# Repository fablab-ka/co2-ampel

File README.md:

# CO2-Ampel V2
![CO2-Ampel][co2ampel]

## Einleitung
Der CO2-Gehalt der Luft kann als Indikator benutzt werden, um das Raumklima zu überwachen und eine potentielle Virenlast in geschlossenen Räumen zu erkennen. In freier Natur und in frisch gelüfteten Räumen beträgt er ungefähr 400ppm (0,04%). In geschlossenen Räumen mit anwesenden Personen steigt er konstant an. Ab ca. 1500ppm wird das Raumklima schlecht, und es können Unbehaglichkeit, Müdigkeit und Konzentrationsschwächen auftreten. 

Da Viren, die als Aerosol übertragen werden, zusammen mit dem CO2 in den Raum gebracht werden, kann über den CO2-Gehalt der Raumluft als Indikator für das Ansteckungsrisiko dienen.

Mithilfe von CO2-Sensoren lässt sich der CO2-Gehalt der Raumluft überwachen. Viele vorhandenen Geräte erlauben zwar eine akkurate Messung, zeigen aber die Auswirkungen auf die Raumluft nur mit kleinen LED-Anzeigen oder überhaupt nicht an. Sie eignen sich daher nur bedingt für den Einsatz in Gruppenräumen.

## Zielsetzung
Die *CO2-Ampel V2* wurde speziell für Schulen und Kitas entwickelt. Sie zeigt das Raumklima spielerisch und gut sichtbar im Stil einer Verkehrsampel an. *Grün* bedeutet *alles in Ordnung*. Springt die Ampel auf *gelb*, wird es Zeit, die Fenster zu öffnen. Bei *rot* ist der Grenzwert überschritten. Ein akustisches Signal weist zusätzlich darauf hin, dass nunmehr umgehend gelüftet werden muss. Sobald der CO2-Gehalt sich normalisiert hat, springt die Ampel wieder auf *grün*. Ein lachender bzw. ein trauriger Smiley illustrieren das Messergebnis zusätzlich.

Das Gerät lässt sich leicht installieren und wird über ein gewöhnliches USB-Kabel mit Strom versorgt. Der eingebaute Sensor erlaubt präzise CO2-Messungen. Auf Wunsch lässt sich der Verlauf der Messwerte per WLAN in einem Web-Interface anzeigen und protokollieren.

Bei der CO2-Ampel V2 handelt es sich um ein gemeinsames Projekt des [FabLab Karlsruhe e.V.](https://fablab-karlsruhe.de) und des [FabLab Bruchsal e.V.](http://fablab-bruchsal.de) im Rahmen der Aktion [Corona-Hilfe Karlsruhe](https://coronahilfe-karlsruhe.de).

## Inbetriebnahme und Fehlerbehebung
Die [Bedienungsanleitung](Documentation/Deutsch/Bedienungsanleitung.md) der CO2-Ampel V2 erläutert alle erforderlichen Schritte zur Inbetriebnahme und zur Nutzung einer fertigen CO2-Ampel. Sie deckt die folgenden Aspekte ab:

* Installation und Stromversorgung
* Optische und akustische Signale
* Konfiguration der WLAN-Verbindung (optional)
* Zugriff auf die Messdaten und Protokolle (optional)
* Fehlerbehebung
* Technische Daten
* Entsorgung

## Aufbauanleitung (Bausatz)
Die bebilderte [Aufbauanleitung](Documentation/Deutsch/Aufbauanleitung.md) erklärt Schritt für Schritt, wie die CO2-Ampel aus den Einzelkomponenten zusammengesetzt wird. Dies umfasst die folgenden Schritte:

* Einstecken des Microcontrollers und des CO2-Sensors
* Einsetzen der Platine
* Zusammenstecken und Verschrauben des Geräts

## Beschaffung bzw. Herstellung der Komponenten
Die [Herstellungsanleitung](Documentation/Deutsch/Herstellungsanleitung.md) gibt einen Überblick, wie die Einzelkomponenten der CO2-Ampel basierend auf den Informationen in diesem GitHub-Repository hergestellt bzw. beschafft werden können. Die Anleitung umfasst die folgenden Abschnitte:

* Beschaffung der Bauteile
* Bestellung der Platine bei einem PCB-Haus
* Bestückung der Platine mit den SMD-Komponenten
* Einlöten der weiteren elektronischen Komponenten
* Kompilieren und Hochladen der Software
* Einrichtung des Webinterfaces für den Datenzugriff
* 3D-Druck des Gehäuses

In der bebilderten [Loetanleitung](Documentation/Deutsch/Loetanleitung) sind alle wichtigen Schritte zum Löten der Komponenten beschrieben. Wir haben uns hier auf das Einlöten der Through Hole Komponenten beschränkt.

## Weiterentwicklung des Projekts
Der gesamte Quellcode der CO2-Ampel V2 wurde in diesem  GitHub-Repository veröffentlicht. Er besteht aus den folgenden Komponenten:

* Platine ([Gerber](https://de.wikipedia.org/wiki/Gerber-Format))
* Software (c++)
* Gehäuse (Wahlweise [Autodesk Fusion 360](https://www.autodesk.de/products/fusion-360/overview) oder [OpenSCAD](https://www.openscad.org))

## Zusätzliche Ressourcen
  * https://wiki.fablab-karlsruhe.de/doku.php?id=projekte:2020:co2-ampel

[co2ampel]: images/co2ampel.jpg "CO2-Ampel"

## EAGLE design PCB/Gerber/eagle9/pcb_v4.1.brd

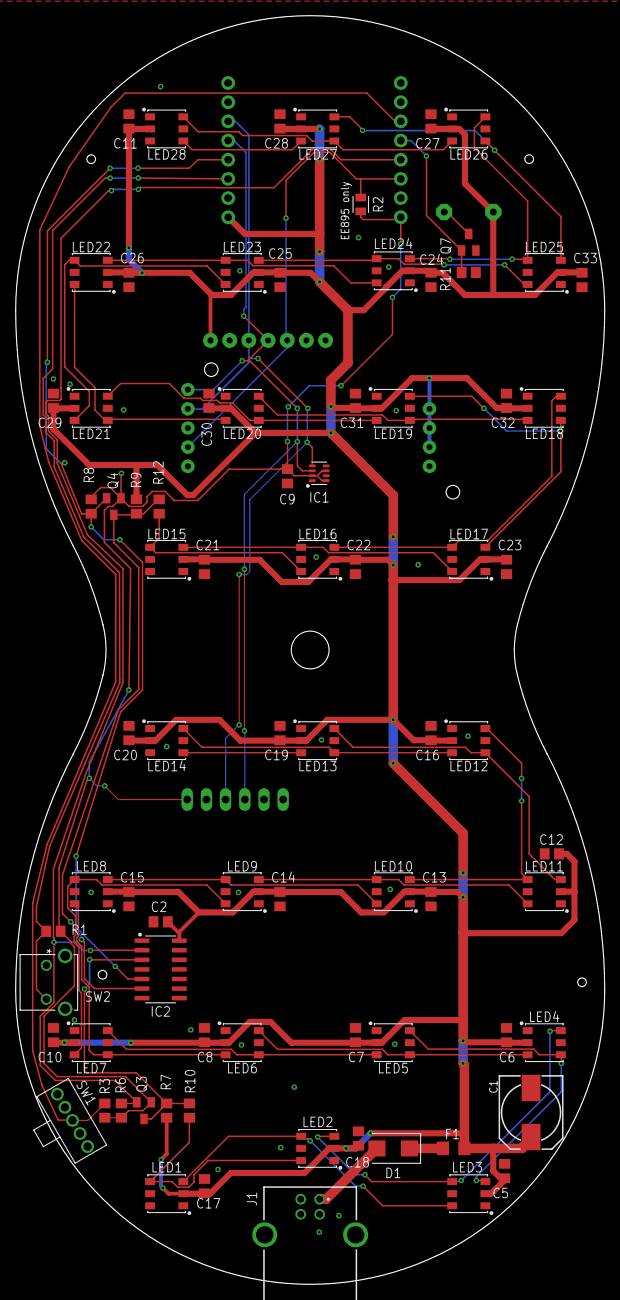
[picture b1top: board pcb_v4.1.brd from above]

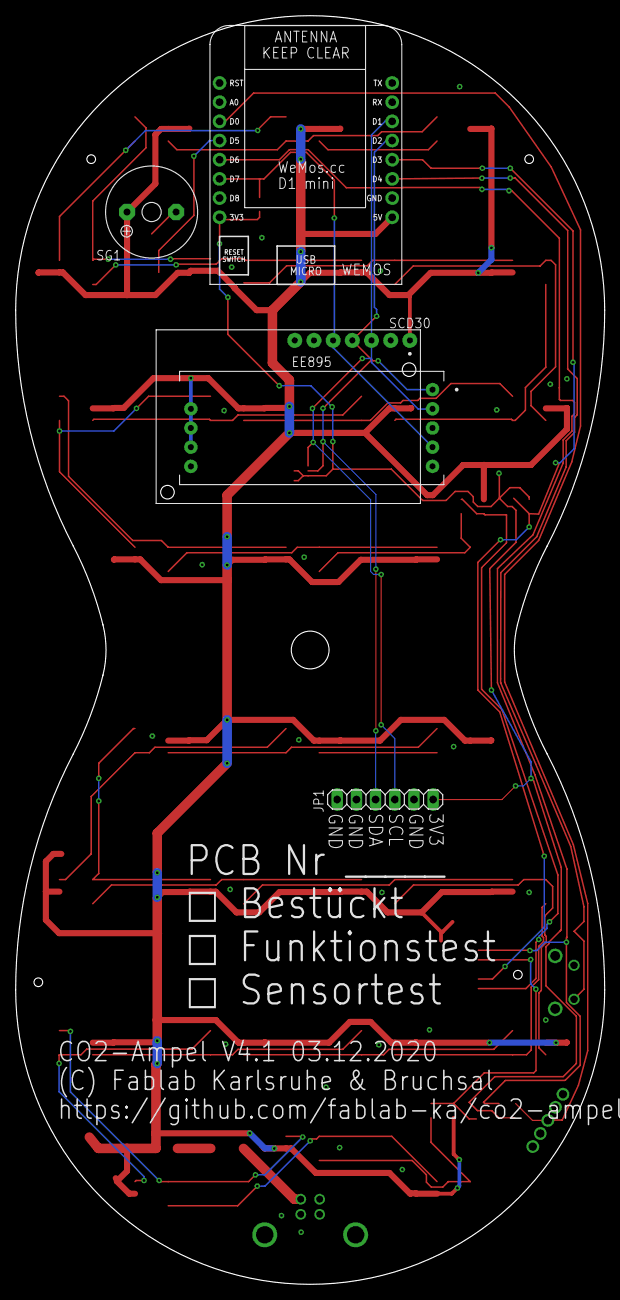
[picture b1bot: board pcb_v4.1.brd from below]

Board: 2 copper layers, 78.0 x 168.0 mm, 84 parts (5 on the bottom side), 44 nets.

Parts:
C1: 1m; 140CLH-0810
C2, C5, C6, C7, C8, C9, C10, C11, C12, C13, C14, C15, C16, C17, C18, C19, C20, C21, C22, C23, C24, C25, C26, C27, C28, C29, C30, C31, C32, C33: 100n; C0805
D1: SS24; DIOM5336X265N
EE895: EE895; DIP3200W60P254L1500H700Q10A
F1: 1206L110THYR; R1206
IC1: BMP280; SON65P200X250X95-8N
IC2: SN74AHCT125; SOIC127P600X175-14N
J1: C46392; 61400416121
JP1: PINHD-1X6; 1X06
LED1, LED2, LED3, LED4, LED5, LED6, LED7, LED8, LED9, LED10, LED11, LED12, LED13, LED14, LED15, LED16, LED17, LED18, LED19, LED20, LED21, LED22, LED23, LED24, LED25, LED26, LED27, LED28: WS2813; SON160P500X500X150-6N
Q3, Q4, Q7: DMG2302UK-7; SOT23
R1, R3, R6, R8, R11: 4.7k; R0805
R2: 4,7k; RESC2012X65
R7, R9: 1k; R0805
R10, R12: 470R; R0805
SCD30: SDC30; HDRV7W80P254_1X7_1778X254X838B
SG1: YS-MBZ12085C05R42; KSS1201
SW1: SWITCH_1X1; HDRRAR5W64P200_1X5_1016X736X556B
SW2: 1-1825027-4; SW2_1825027-E
WEMOS: WEMOS_D1_MINI; HDRVR8W64P254_1X8_2032X254X850B

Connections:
+3V3: C9.1, IC1.2, IC1.6, IC1.8, JP1.1, Q3.1, Q4.1, R1.2, R2.2, R3.2, R6.2, R8.2, WEMOS.3V3
+5V: C1.+, C2.1, C5.1, C6.1, C7.1, C8.1, C10.1, C11.1, C12.1, C13.1, C14.1, C15.1, C16.1, C17.1, C18.1, C19.1, C20.1, C21.1, C22.1, C23.1, C24.1, C25.1, C26.1, C27.1, C28.1, C29.1, C30.1, C31.1, C32.1, C33.1, EE895.7, EE895.8, EE895.9, F1.2, IC2.14, LED1.2, LED2.2, LED3.2, LED4.2, LED5.2, LED6.2, LED7.2, LED8.2, LED9.2, LED10.2, LED11.2, LED12.2, LED13.2, LED14.2, LED15.2, LED16.2, LED17.2, LED18.2, LED19.2, LED20.2, LED21.2, LED22.2, LED23.2, LED24.2, LED25.2, LED26.2, LED27.2, LED28.2, R7.2, R9.2, SCD30.1, SG1.+, WEMOS.5V
BUZZER: Q7.1, R11.2, WEMOS.D5
BUZZ_EN: R3.1, SW1.3, WEMOS.D0
GND: C1.-, C2.2, C5.2, C6.2, C7.2, C8.2, C9.2, C10.2, C11.2, C12.2, C13.2, C14.2, C15.2, C16.2, C17.2, C18.2, C19.2, C20.2, C21.2, C22.2, C23.2, C24.2, C25.2, C26.2, C27.2, C28.2, C29.2, C30.2, C31.2, C32.2, C33.2, EE895.3, EE895.5, EE895.6, IC1.1, IC1.5, IC1.7, IC2.1, IC2.4, IC2.7, IC2.10, IC2.13, J1.4, JP1.2, JP1.5, JP1.6, LED1.5, LED1.6, LED2.5, LED3.5, LED4.5, LED5.5, LED6.5, LED7.5, LED8.5, LED9.5, LED10.5, LED11.5, LED12.5, LED13.5, LED14.5, LED15.5, LED15.6, LED16.5, LED17.5, LED18.5, LED19.5, LED20.5, LED21.5, LED22.5, LED23.5, LED24.5, LED25.5, LED26.5, LED27.5, LED28.5, Q7.2, R11.1, SCD30.2, SW1.4, SW2.1, WEMOS.GND
LED_DATA_1: IC2.2, Q3.2, R6.1, WEMOS.D6
LED_DATA_2: IC2.5, Q4.2, R8.1, WEMOS.D3
unnamed: IC2.3, Q3.3, R7.1, R10.1
unnamed: LED2.3, LED3.4, LED4.6
unnamed: LED1.3, LED2.4, LED3.6
unnamed: LED4.3, LED5.4, LED6.6
unnamed: D1.1, F1.1
unnamed: LED3.3, LED4.4, LED5.6
unnamed: LED8.3, LED9.4, LED10.6
unnamed: LED5.3, LED6.4, LED7.6
unnamed: LED6.3, LED7.4, LED8.6
unnamed: LED7.3, LED8.4, LED9.6
unnamed: LED16.3, LED17.4, LED18.6
unnamed: LED9.3, LED10.4, LED11.6
unnamed: LED10.3, LED11.4, LED12.6
unnamed: LED11.3, LED12.4, LED13.6
unnamed: LED12.3, LED13.4, LED14.6
unnamed: LED13.3, LED14.4
unnamed: LED15.4, LED16.6, R12.2
unnamed: LED15.3, LED16.4, LED17.6
unnamed: LED24.3, LED25.4, LED26.6
unnamed: D1.2, J1.1
unnamed: LED17.3, LED18.4, LED19.6
unnamed: LED18.3, LED19.4, LED20.6
unnamed: LED19.3, LED20.4, LED21.6
unnamed: LED20.3, LED21.4, LED22.6
unnamed: LED21.3, LED22.4, LED23.6
unnamed: LED22.3, LED23.4, LED24.6
unnamed: LED23.3, LED24.4, LED25.6
unnamed: Q7.3, SG1.-
unnamed: LED25.3, LED26.4, LED27.6
unnamed: LED26.3, LED27.4, LED28.6
unnamed: LED27.3, LED28.4
RDY: EE895.4, R2.1, SCD30.5, WEMOS.D7
SCHALTER: R1.1, SW2.2, WEMOS.D4
SCL: EE895.2, IC1.4, JP1.3, SCD30.3, WEMOS.D1
SCL1: LED1.4, LED2.6, R10.2
SCL2: IC2.6, Q4.3, R9.1, R12.1
SDA: EE895.1, IC1.3, JP1.4, SCD30.4, WEMOS.D2

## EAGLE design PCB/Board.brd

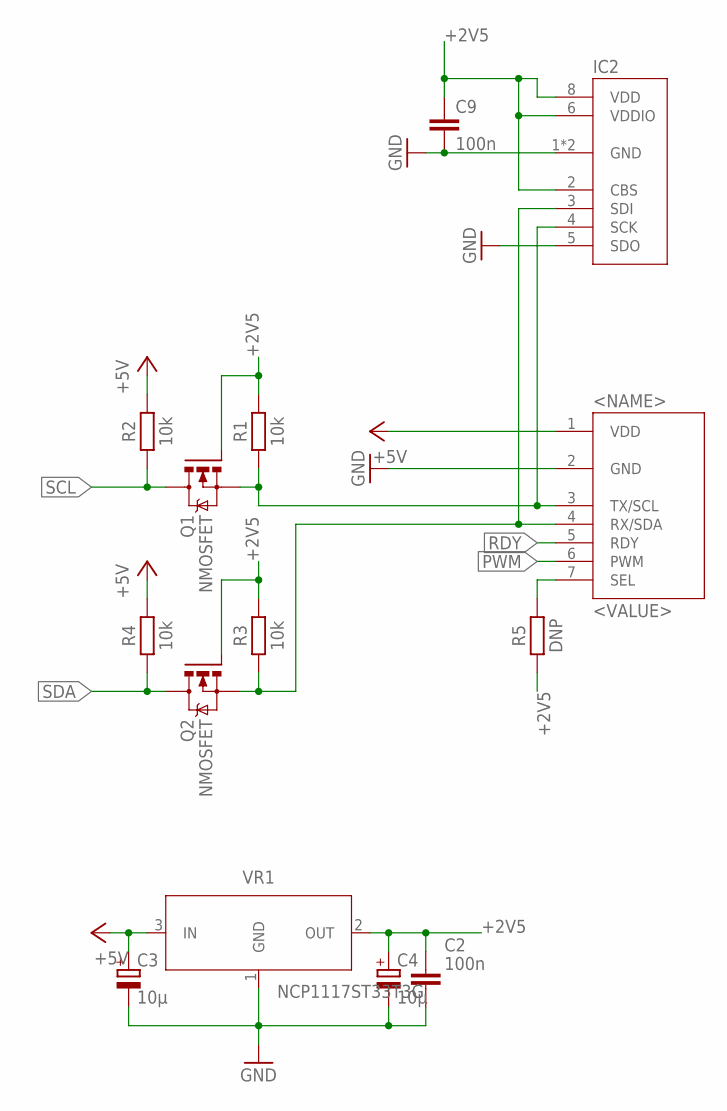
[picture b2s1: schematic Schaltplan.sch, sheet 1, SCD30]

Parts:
C2: 100n; CAPC1608X85
C3, C4: 10µ; 153CLV-0505
C9: 100n; C0603
IC2: BMP280; SON65P200X250X95-8N
Q1, Q2: NMOSFET; SOT23
R1, R2, R3, R4: 10k; RESC1608X60
R5: DNP; RESC1608X60
U$1: SDC30; HDRV7W80P254_1X7_1778X254X838B
VR1: NCP1117ST33T3G; SOT230P700X170-4

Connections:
+2V5: C2.1, C4.+, C9.1, IC2.2 (CBS), IC2.6 (VDDIO), IC2.8 (VDD), Q1.1 (G), Q2.1 (G), R1.2, R3.2, R5.1, VR1.2 (OUT)
+5V: C3.+, R2.2, R4.2, U$1.1 (VDD), VR1.3 (IN); also elsewhere on the board
GND: C2.2, C3.-, C4.-, C9.2, IC2.1 (GND), IC2.5 (SDO), IC2.7 (GND), U$1.2 (GND), VR1.1 (GND); also elsewhere on the board
unnamed: IC2.4 (SCK), Q1.2 (S), R1.1, U$1.3 (TX/SCL)
unnamed: R5.2, U$1.7 (SEL)
unnamed: IC2.3 (SDI), Q2.2 (S), R3.1, U$1.4 (RX/SDA)
PWM: U$1.6 (PWM); also elsewhere on the board
RDY: U$1.5 (RDY); also elsewhere on the board
SCL: Q1.3 (D), R2.1; also elsewhere on the board
SDA: Q2.3 (D), R4.1; also elsewhere on the board

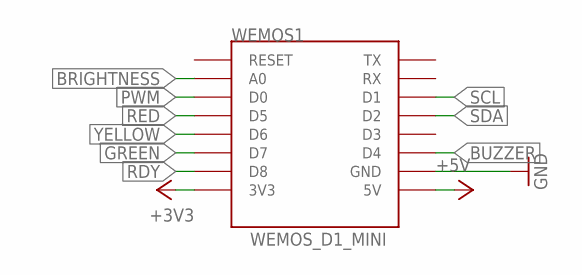
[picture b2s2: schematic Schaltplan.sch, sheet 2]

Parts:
WEMOS1: WEMOS_D1_MINI; HDRVR8W64P254_1X8_2032X254X850B

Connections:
+3V3: WEMOS1.3V3
+5V: WEMOS1.5V; also elsewhere on the board
BRIGHTNESS: WEMOS1.A0; also elsewhere on the board
BUZZER: WEMOS1.D4; also elsewhere on the board
GND: WEMOS1.GND; also elsewhere on the board
GREEN: WEMOS1.D7; also elsewhere on the board
PWM: WEMOS1.D0; also elsewhere on the board
RDY: WEMOS1.D8; also elsewhere on the board
RED: WEMOS1.D5; also elsewhere on the board
SCL: WEMOS1.D1; also elsewhere on the board
SDA: WEMOS1.D2; also elsewhere on the board
YELLOW: WEMOS1.D6; also elsewhere on the board

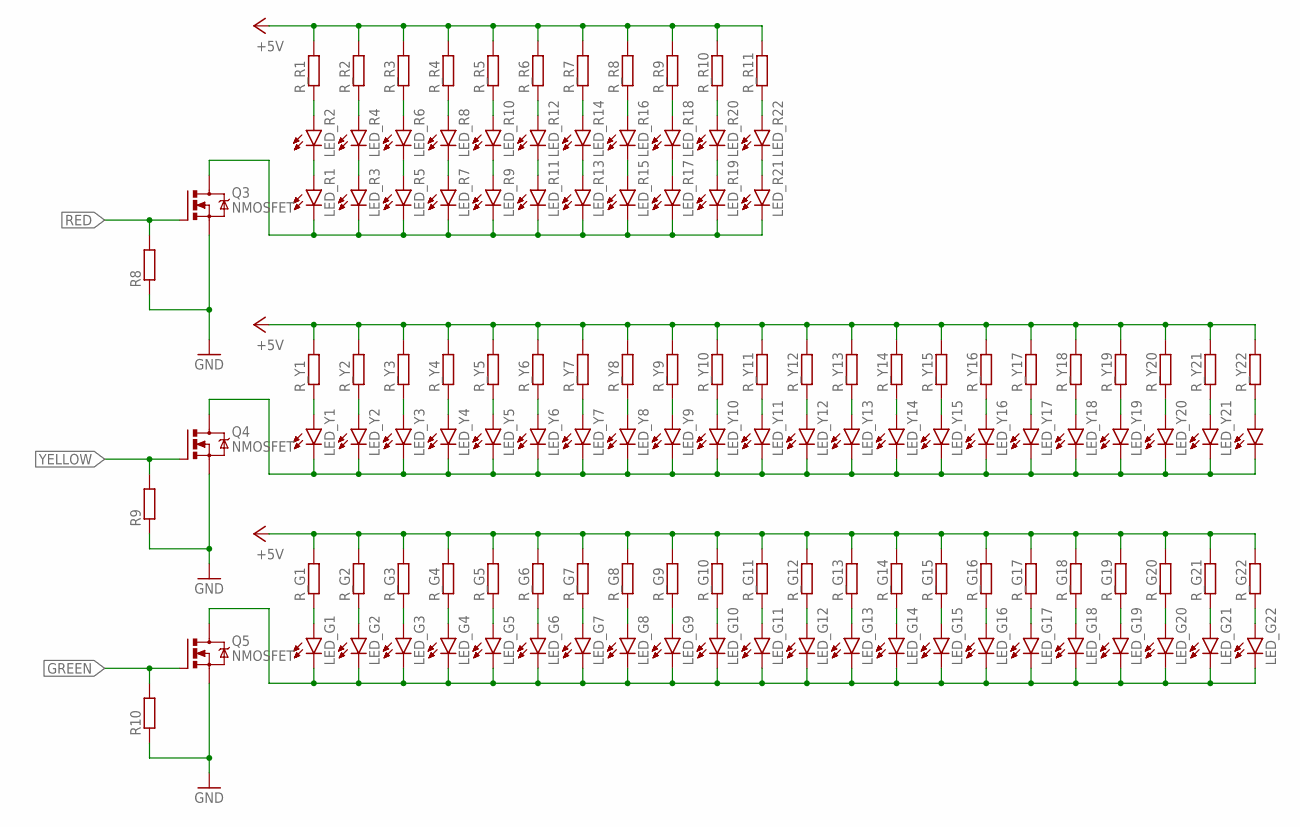
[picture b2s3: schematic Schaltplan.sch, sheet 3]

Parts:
LED_G1, LED_G2, LED_G3, LED_G4, LED_G5, LED_G6, LED_G7, LED_G8, LED_G9, LED_G10, LED_G11, LED_G12, LED_G13, LED_G14, LED_G15, LED_G16, LED_G17, LED_G18, LED_G19, LED_G20, LED_G21, LED_G22: LEDCHIP-LED0805; CHIP-LED0805
LED_R1, LED_R2, LED_R3, LED_R4, LED_R5, LED_R6, LED_R7, LED_R8, LED_R9, LED_R10, LED_R11, LED_R12, LED_R13, LED_R14, LED_R15, LED_R16, LED_R17, LED_R18, LED_R19, LED_R20, LED_R21, LED_R22: LEDCHIP-LED0805; CHIP-LED0805
LED_Y1, LED_Y2, LED_Y3, LED_Y4, LED_Y5, LED_Y6, LED_Y7, LED_Y8, LED_Y9, LED_Y10, LED_Y11, LED_Y12, LED_Y13, LED_Y14, LED_Y15, LED_Y16, LED_Y17, LED_Y18, LED_Y19, LED_Y20, LED_Y21, LED_Y22: LEDCHIP-LED0805; CHIP-LED0805
Q3, Q4, Q5: NMOSFET; SOT23
R8, R9, R10: R-EU_R0805; R0805
R_G1, R_G2, R_G3, R_G4, R_G5, R_G6, R_G7, R_G8, R_G9, R_G10, R_G11, R_G12, R_G13, R_G14, R_G15, R_G16, R_G17, R_G18, R_G19, R_G20, R_G21, R_G22: R-EU_R0805; R0805
R_R1, R_R2, R_R3, R_R4, R_R5, R_R6, R_R7, R_R8, R_R9, R_R10, R_R11: R-EU_R0805; R0805
R_Y1, R_Y2, R_Y3, R_Y4, R_Y5, R_Y6, R_Y7, R_Y8, R_Y9, R_Y10, R_Y11, R_Y12, R_Y13, R_Y14, R_Y15, R_Y16, R_Y17, R_Y18, R_Y19, R_Y20, R_Y21, R_Y22: R-EU_R0805; R0805

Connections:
+5V: R_G1.2, R_G2.2, R_G3.2, R_G4.2, R_G5.2, R_G6.2, R_G7.2, R_G8.2, R_G9.2, R_G10.2, R_G11.2, R_G12.2, R_G13.2, R_G14.2, R_G15.2, R_G16.2, R_G17.2, R_G18.2, R_G19.2, R_G20.2, R_G21.2, R_G22.2, R_R1.2, R_R2.2, R_R3.2, R_R4.2, R_R5.2, R_R6.2, R_R7.2, R_R8.2, R_R9.2, R_R10.2, R_R11.2, R_Y1.2, R_Y2.2, R_Y3.2, R_Y4.2, R_Y5.2, R_Y6.2, R_Y7.2, R_Y8.2, R_Y9.2, R_Y10.2, R_Y11.2, R_Y12.2, R_Y13.2, R_Y14.2, R_Y15.2, R_Y16.2, R_Y17.2, R_Y18.2, R_Y19.2, R_Y20.2, R_Y21.2, R_Y22.2; also elsewhere on the board
GND: Q3.2 (S), Q4.2 (S), Q5.2 (S), R8.1, R9.1, R10.1; also elsewhere on the board
GREEN: Q5.1 (G), R10.2; also elsewhere on the board
unnamed: LED_G1.A, R_G1.1
unnamed: LED_R3.A, LED_R4.C
unnamed: LED_R4.A, R_R2.1
unnamed: LED_R5.A, LED_R6.C
unnamed: LED_R1.C, LED_R3.C, LED_R5.C, LED_R7.C, LED_R9.C, LED_R11.C, LED_R13.C, LED_R15.C, LED_R17.C, LED_R19.C, LED_R21.C, Q3.3 (D)
unnamed: LED_Y1.C, LED_Y2.C, LED_Y3.C, LED_Y4.C, LED_Y5.C, LED_Y6.C, LED_Y7.C, LED_Y8.C, LED_Y9.C, LED_Y10.C, LED_Y11.C, LED_Y12.C, LED_Y13.C, LED_Y14.C, LED_Y15.C, LED_Y16.C, LED_Y17.C, LED_Y18.C, LED_Y19.C, LED_Y20.C, LED_Y21.C, LED_Y22.C, Q4.3 (D)
unnamed: LED_G1.C, LED_G2.C, LED_G3.C, LED_G4.C, LED_G5.C, LED_G6.C, LED_G7.C, LED_G8.C, LED_G9.C, LED_G10.C, LED_G11.C, LED_G12.C, LED_G13.C, LED_G14.C, LED_G15.C, LED_G16.C, LED_G17.C, LED_G18.C, LED_G19.C, LED_G20.C, LED_G21.C, LED_G22.C, Q5.3 (D)
unnamed: LED_Y1.A, R_Y1.1
unnamed: LED_R1.A, LED_R2.C
unnamed: LED_R2.A, R_R1.1
unnamed: LED_R6.A, R_R3.1
unnamed: LED_R7.A, LED_R8.C
unnamed: LED_R8.A, R_R4.1
unnamed: LED_R9.A, LED_R10.C
unnamed: LED_R10.A, R_R5.1
unnamed: LED_R11.A, LED_R12.C
unnamed: LED_R12.A, R_R6.1
unnamed: LED_R13.A, LED_R14.C
unnamed: LED_R14.A, R_R7.1
unnamed: LED_R15.A, LED_R16.C
unnamed: LED_R16.A, R_R8.1
unnamed: LED_R17.A, LED_R18.C
unnamed: LED_R18.A, R_R9.1
unnamed: LED_R19.A, LED_R20.C
unnamed: LED_R20.A, R_R10.1
unnamed: LED_R21.A, LED_R22.C
unnamed: LED_R22.A, R_R11.1
unnamed: LED_Y2.A, R_Y2.1
unnamed: LED_Y3.A, R_Y3.1
unnamed: LED_Y4.A, R_Y4.1
unnamed: LED_Y5.A, R_Y5.1
unnamed: LED_Y6.A, R_Y6.1
unnamed: LED_Y7.A, R_Y7.1
unnamed: LED_Y8.A, R_Y8.1
unnamed: LED_Y9.A, R_Y9.1
unnamed: LED_Y10.A, R_Y10.1
unnamed: LED_Y11.A, R_Y11.1
unnamed: LED_Y12.A, R_Y12.1
unnamed: LED_Y13.A, R_Y13.1
unnamed: LED_Y14.A, R_Y14.1
unnamed: LED_Y15.A, R_Y15.1
unnamed: LED_Y16.A, R_Y16.1
unnamed: LED_Y17.A, R_Y17.1
unnamed: LED_Y18.A, R_Y18.1
unnamed: LED_Y19.A, R_Y19.1
unnamed: LED_Y20.A, R_Y20.1
unnamed: LED_Y21.A, R_Y21.1
unnamed: LED_Y22.A, R_Y22.1
unnamed: LED_G2.A, R_G2.1
unnamed: LED_G3.A, R_G3.1
unnamed: LED_G4.A, R_G4.1
unnamed: LED_G5.A, R_G5.1
unnamed: LED_G6.A, R_G6.1
unnamed: LED_G7.A, R_G7.1
unnamed: LED_G8.A, R_G8.1
unnamed: LED_G9.A, R_G9.1
unnamed: LED_G10.A, R_G10.1
unnamed: LED_G11.A, R_G11.1
unnamed: LED_G12.A, R_G12.1
unnamed: LED_G13.A, R_G13.1
unnamed: LED_G14.A, R_G14.1
unnamed: LED_G15.A, R_G15.1
unnamed: LED_G16.A, R_G16.1
unnamed: LED_G17.A, R_G17.1
unnamed: LED_G18.A, R_G18.1
unnamed: LED_G19.A, R_G19.1
unnamed: LED_G20.A, R_G20.1
unnamed: LED_G21.A, R_G21.1
unnamed: LED_G22.A, R_G22.1
RED: Q3.1 (G), R8.2; also elsewhere on the board
YELLOW: Q4.1 (G), R9.2; also elsewhere on the board

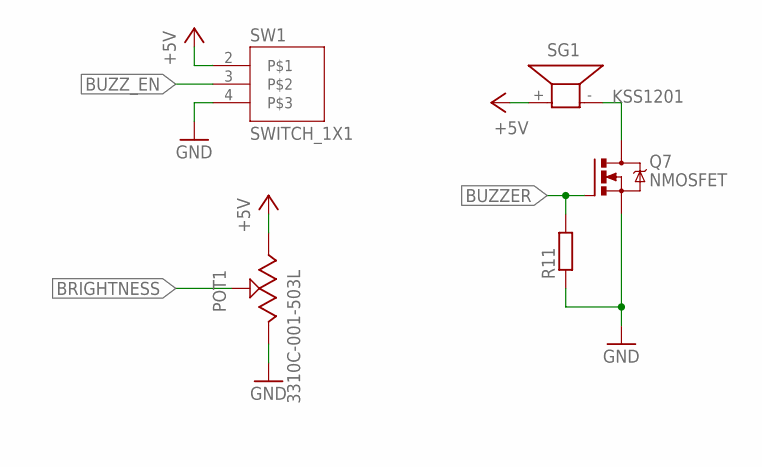
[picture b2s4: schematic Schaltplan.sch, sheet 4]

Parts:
POT1: 3310C-001-503L
Q7: NMOSFET; SOT23
R11: R-EU_R0805; R0805
SG1: KSS1201
SW1: SWITCH_1X1; HDRRAR5W64P200_1X5_1016X736X556B

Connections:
+5V: POT1.3, SG1.+ (1), SW1.2; also elsewhere on the board
BRIGHTNESS: POT1.2; also elsewhere on the board
BUZZER: Q7.1 (G), R11.2; also elsewhere on the board
BUZZ_EN: SW1.3; also elsewhere on the board
GND: POT1.1, Q7.2 (S), R11.1, SW1.4; also elsewhere on the board
unnamed: Q7.3 (D), SG1.- (2)

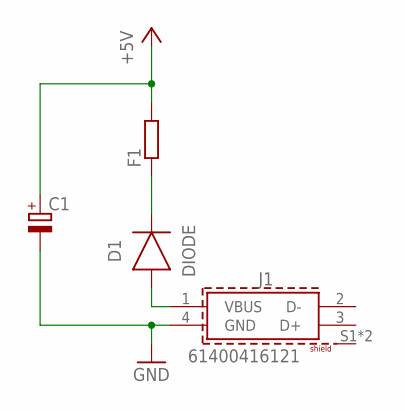
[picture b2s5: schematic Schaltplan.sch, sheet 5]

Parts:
C1: CPOL-EUF; PANASONIC_F
D1: DIODE; DIOM5226X290N
F1: R-EU_R1206; R1206
J1: 61400416121

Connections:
+5V: C1.+, F1.2; also elsewhere on the board
GND: C1.-, J1.4 (GND); also elsewhere on the board
unnamed 17: D1.1 (C), F1.1; also elsewhere on the board

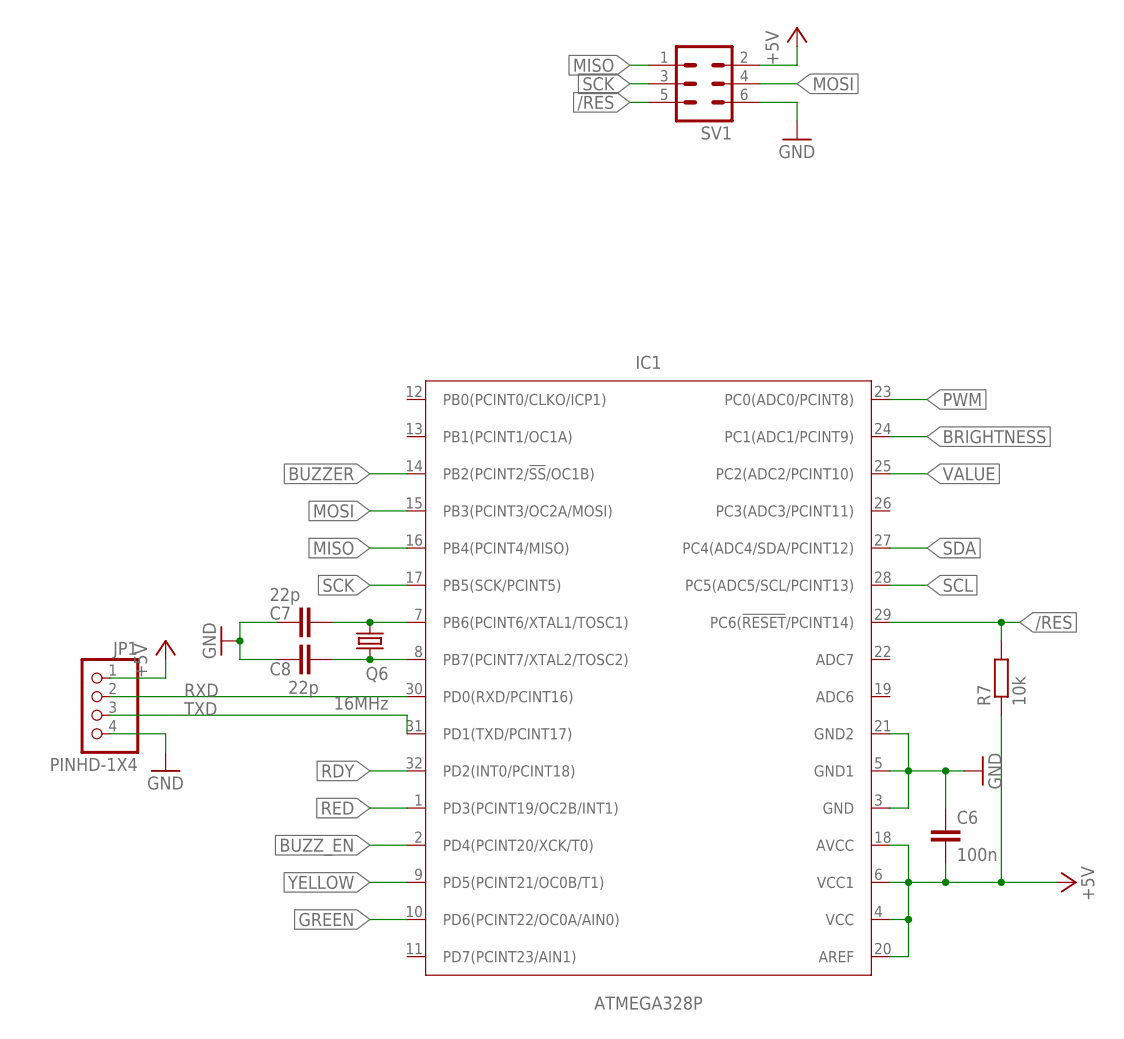
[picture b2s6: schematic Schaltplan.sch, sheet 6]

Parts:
C6: 100n; C0603
C7, C8: 22p; C0603
IC1: ATMEGA328P; TQFP32-08
JP1: PINHD-1X4; 1X04
Q6: 16MHz; HC49UP
R7: 10k; R0805
SV1: ML6

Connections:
+5V: C6.2, IC1.4 (VCC), IC1.6 (VCC1), IC1.18 (AVCC), IC1.20 (AREF), JP1.1, R7.1, SV1.2; also elsewhere on the board
/RES: IC1.29 (PC6(!RESET!/PCINT14)), R7.2, SV1.5
BRIGHTNESS: IC1.24 (PC1(ADC1/PCINT9)); also elsewhere on the board
BUZZER: IC1.14 (PB2(PCINT2/!SS!/OC1B)); also elsewhere on the board
BUZZ_EN: IC1.2 (PD4(PCINT20/XCK/T0)); also elsewhere on the board
GND: C6.1, C7.1, C8.1, IC1.3 (GND), IC1.5 (GND1), IC1.21 (GND2), JP1.4, SV1.6; also elsewhere on the board
GREEN: IC1.10 (PD6(PCINT22/OC0A/AIN0)); also elsewhere on the board
MISO: IC1.16 (PB4(PCINT4/MISO)), SV1.1
MOSI: IC1.15 (PB3(PCINT3/OC2A/MOSI)), SV1.4
unnamed: C7.2, IC1.7 (PB6(PCINT6/XTAL1/TOSC1)), Q6.2
unnamed: C8.2, IC1.8 (PB7(PCINT7/XTAL2/TOSC2)), Q6.1
PWM: IC1.23 (PC0(ADC0/PCINT8)); also elsewhere on the board
RDY: IC1.32 (PD2(INT0/PCINT18)); also elsewhere on the board
RED: IC1.1 (PD3(PCINT19/OC2B/INT1)); also elsewhere on the board
RXD: IC1.30 (PD0(RXD/PCINT16)), JP1.2
SCK: IC1.17 (PB5(SCK/PCINT5)), SV1.3
SCL: IC1.28 (PC5(ADC5/SCL/PCINT13)); also elsewhere on the board
SDA: IC1.27 (PC4(ADC4/SDA/PCINT12)); also elsewhere on the board
TXD: IC1.31 (PD1(TXD/PCINT17)), JP1.3
VALUE: IC1.25 (PC2(ADC2/PCINT10))
YELLOW: IC1.9 (PD5(PCINT21/OC0B/T1)); also elsewhere on the board

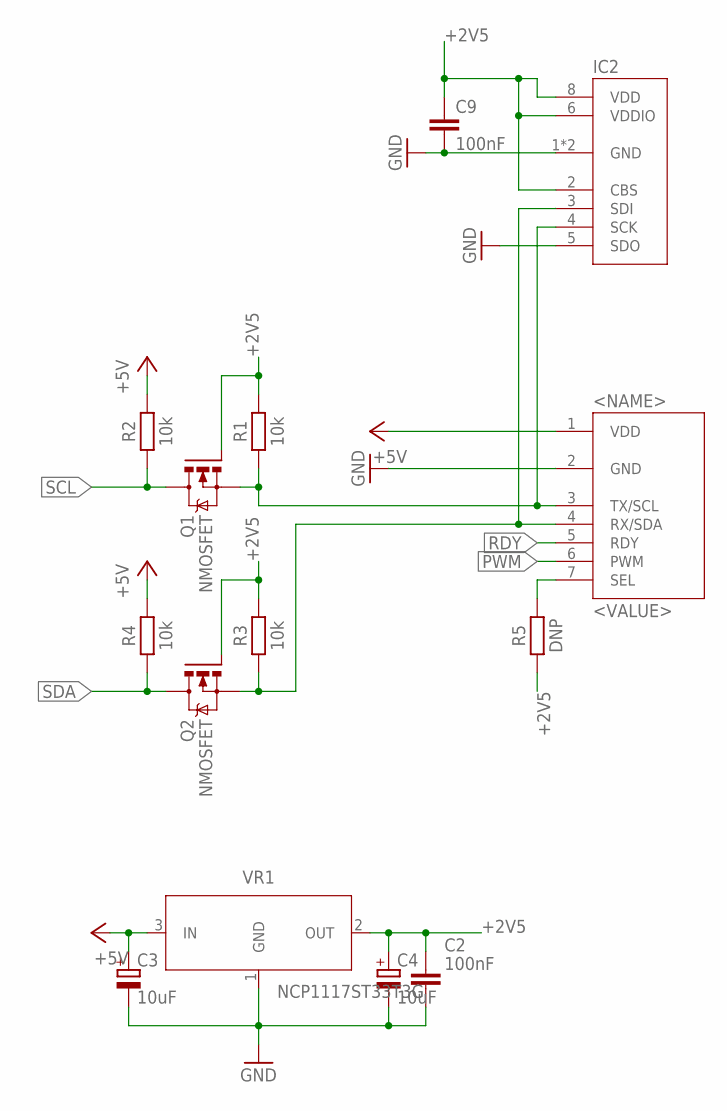
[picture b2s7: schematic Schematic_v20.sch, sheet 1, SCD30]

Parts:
C2: 100nF; CAPC1608X85
C3, C4: 10uF; 153CLV-0505
C9: 100nF; C0603
IC2: BMP280; SON65P200X250X95-8N
Q1, Q2: NMOSFET; SOT23
R1, R2, R3, R4: 10k; RESC1608X60
R5: DNP; RESC1608X60
U$1: SDC30; HDRV7W80P254_1X7_1778X254X838B
VR1: NCP1117ST33T3G; SOT230P700X170-4

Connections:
+2V5: C2.1, C4.+, C9.1, IC2.2 (CBS), IC2.6 (VDDIO), IC2.8 (VDD), Q1.1 (G), Q2.1 (G), R1.2, R3.2, R5.1, VR1.2 (OUT)
+5V: C3.+, R2.2, R4.2, U$1.1 (VDD), VR1.3 (IN); also elsewhere on the board
GND: C2.2, C3.-, C4.-, C9.2, IC2.1 (GND), IC2.5 (SDO), IC2.7 (GND), U$1.2 (GND), VR1.1 (GND); also elsewhere on the board
unnamed: IC2.4 (SCK), Q1.2 (S), R1.1, U$1.3 (TX/SCL)
unnamed: R5.2, U$1.7 (SEL)
unnamed: IC2.3 (SDI), Q2.2 (S), R3.1, U$1.4 (RX/SDA)
PWM: U$1.6 (PWM); also elsewhere on the board
RDY: U$1.5 (RDY); also elsewhere on the board
SCL: Q1.3 (D), R2.1; also elsewhere on the board
SDA: Q2.3 (D), R4.1; also elsewhere on the board

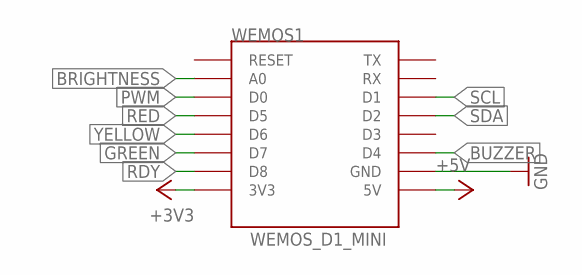
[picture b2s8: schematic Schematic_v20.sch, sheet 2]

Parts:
WEMOS1: WEMOS_D1_MINI; HDRVR8W64P254_1X8_2032X254X850B

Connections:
+3V3: WEMOS1.3V3
+5V: WEMOS1.5V; also elsewhere on the board
BRIGHTNESS: WEMOS1.A0; also elsewhere on the board
BUZZER: WEMOS1.D4; also elsewhere on the board
GND: WEMOS1.GND; also elsewhere on the board
GREEN: WEMOS1.D7; also elsewhere on the board
PWM: WEMOS1.D0; also elsewhere on the board
RDY: WEMOS1.D8; also elsewhere on the board
RED: WEMOS1.D5; also elsewhere on the board
SCL: WEMOS1.D1; also elsewhere on the board
SDA: WEMOS1.D2; also elsewhere on the board
YELLOW: WEMOS1.D6; also elsewhere on the board

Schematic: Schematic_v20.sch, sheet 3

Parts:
LED_G1, LED_G2, LED_G3, LED_G4, LED_G5, LED_G6, LED_G7, LED_G8, LED_G9, LED_G10, LED_G11, LED_G12, LED_G13, LED_G14, LED_G15, LED_G16, LED_G17, LED_G18, LED_G19, LED_G20, LED_G21, LED_G22: LEDCHIP-LED0805; CHIP-LED0805
LED_R1, LED_R2, LED_R3, LED_R4, LED_R5, LED_R6, LED_R7, LED_R8, LED_R9, LED_R10, LED_R11, LED_R12, LED_R13, LED_R14, LED_R15, LED_R16, LED_R17, LED_R18, LED_R19, LED_R20, LED_R21, LED_R22: LEDCHIP-LED0805; CHIP-LED0805
LED_Y1, LED_Y2, LED_Y3, LED_Y4, LED_Y5, LED_Y6, LED_Y7, LED_Y8, LED_Y9, LED_Y10, LED_Y11, LED_Y12, LED_Y13, LED_Y14, LED_Y15, LED_Y16, LED_Y17, LED_Y18, LED_Y19, LED_Y20, LED_Y21, LED_Y22: LEDCHIP-LED0805; CHIP-LED0805
Q3, Q4, Q5: NMOSFET; SOT23
R_G1, R_G2, R_G3, R_G4, R_G5, R_G6, R_G7, R_G8, R_G9, R_G10, R_G11, R_G12, R_G13, R_G14, R_G15, R_G16, R_G17, R_G18, R_G19, R_G20, R_G21, R_G22: R-EU_R0805; R0805
R_R1, R_R2, R_R3, R_R4, R_R5, R_R6, R_R7, R_R8, R_R9, R_R10, R_R11: R-EU_R0805; R0805
R_Y1, R_Y2, R_Y3, R_Y4, R_Y5, R_Y6, R_Y7, R_Y8, R_Y9, R_Y10, R_Y11, R_Y12, R_Y13, R_Y14, R_Y15, R_Y16, R_Y17, R_Y18, R_Y19, R_Y20, R_Y21, R_Y22: R-EU_R0805; R0805

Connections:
+5V: R_G1.2, R_G2.2, R_G3.2, R_G4.2, R_G5.2, R_G6.2, R_G7.2, R_G8.2, R_G9.2, R_G10.2, R_G11.2, R_G12.2, R_G13.2, R_G14.2, R_G15.2, R_G16.2, R_G17.2, R_G18.2, R_G19.2, R_G20.2, R_G21.2, R_G22.2, R_R1.2, R_R2.2, R_R3.2, R_R4.2, R_R5.2, R_R6.2, R_R7.2, R_R8.2, R_R9.2, R_R10.2, R_R11.2, R_Y1.2, R_Y2.2, R_Y3.2, R_Y4.2, R_Y5.2, R_Y6.2, R_Y7.2, R_Y8.2, R_Y9.2, R_Y10.2, R_Y11.2, R_Y12.2, R_Y13.2, R_Y14.2, R_Y15.2, R_Y16.2, R_Y17.2, R_Y18.2, R_Y19.2, R_Y20.2, R_Y21.2, R_Y22.2; also elsewhere on the board
GND: Q3.2 (S), Q4.2 (S), Q5.2 (S); also elsewhere on the board
GREEN: Q5.1 (G); also elsewhere on the board
unnamed: LED_G1.A, R_G1.1
unnamed: LED_R3.A, LED_R4.C
unnamed: LED_R4.A, R_R2.1
unnamed: LED_R5.A, LED_R6.C
unnamed: LED_R1.C, LED_R3.C, LED_R5.C, LED_R7.C, LED_R9.C, LED_R11.C, LED_R13.C, LED_R15.C, LED_R17.C, LED_R19.C, LED_R21.C, Q3.3 (D)
unnamed: LED_Y1.C, LED_Y2.C, LED_Y3.C, LED_Y4.C, LED_Y5.C, LED_Y6.C, LED_Y7.C, LED_Y8.C, LED_Y9.C, LED_Y10.C, LED_Y11.C, LED_Y12.C, LED_Y13.C, LED_Y14.C, LED_Y15.C, LED_Y16.C, LED_Y17.C, LED_Y18.C, LED_Y19.C, LED_Y20.C, LED_Y21.C, LED_Y22.C, Q4.3 (D)
unnamed: LED_G1.C, LED_G2.C, LED_G3.C, LED_G4.C, LED_G5.C, LED_G6.C, LED_G7.C, LED_G8.C, LED_G9.C, LED_G10.C, LED_G11.C, LED_G12.C, LED_G13.C, LED_G14.C, LED_G15.C, LED_G16.C, LED_G17.C, LED_G18.C, LED_G19.C, LED_G20.C, LED_G21.C, LED_G22.C, Q5.3 (D)
unnamed: LED_Y1.A, R_Y1.1
unnamed: LED_R1.A, LED_R2.C
unnamed: LED_R2.A, R_R1.1
unnamed: LED_R6.A, R_R3.1
unnamed: LED_R7.A, LED_R8.C
unnamed: LED_R8.A, R_R4.1
unnamed: LED_R9.A, LED_R10.C
unnamed: LED_R10.A, R_R5.1
unnamed: LED_R11.A, LED_R12.C
unnamed: LED_R12.A, R_R6.1
unnamed: LED_R13.A, LED_R14.C
unnamed: LED_R14.A, R_R7.1
unnamed: LED_R15.A, LED_R16.C
unnamed: LED_R16.A, R_R8.1
unnamed: LED_R17.A, LED_R18.C
unnamed: LED_R18.A, R_R9.1
unnamed: LED_R19.A, LED_R20.C
unnamed: LED_R20.A, R_R10.1
unnamed: LED_R21.A, LED_R22.C
unnamed: LED_R22.A, R_R11.1
unnamed: LED_Y2.A, R_Y2.1
unnamed: LED_Y3.A, R_Y3.1
unnamed: LED_Y4.A, R_Y4.1
unnamed: LED_Y5.A, R_Y5.1
unnamed: LED_Y6.A, R_Y6.1
unnamed: LED_Y7.A, R_Y7.1
unnamed: LED_Y8.A, R_Y8.1
unnamed: LED_Y9.A, R_Y9.1
unnamed: LED_Y10.A, R_Y10.1
unnamed: LED_Y11.A, R_Y11.1
unnamed: LED_Y12.A, R_Y12.1
unnamed: LED_Y13.A, R_Y13.1
unnamed: LED_Y14.A, R_Y14.1
unnamed: LED_Y15.A, R_Y15.1
unnamed: LED_Y16.A, R_Y16.1
unnamed: LED_Y17.A, R_Y17.1
unnamed: LED_Y18.A, R_Y18.1
unnamed: LED_Y19.A, R_Y19.1
unnamed: LED_Y20.A, R_Y20.1
unnamed: LED_Y21.A, R_Y21.1
unnamed: LED_Y22.A, R_Y22.1
unnamed: LED_G2.A, R_G2.1
unnamed: LED_G3.A, R_G3.1
unnamed: LED_G4.A, R_G4.1
unnamed: LED_G5.A, R_G5.1
unnamed: LED_G6.A, R_G6.1
unnamed: LED_G7.A, R_G7.1
unnamed: LED_G8.A, R_G8.1
unnamed: LED_G9.A, R_G9.1
unnamed: LED_G10.A, R_G10.1
unnamed: LED_G11.A, R_G11.1
unnamed: LED_G12.A, R_G12.1
unnamed: LED_G13.A, R_G13.1
unnamed: LED_G14.A, R_G14.1
unnamed: LED_G15.A, R_G15.1
unnamed: LED_G16.A, R_G16.1
unnamed: LED_G17.A, R_G17.1
unnamed: LED_G18.A, R_G18.1
unnamed: LED_G19.A, R_G19.1
unnamed: LED_G20.A, R_G20.1
unnamed: LED_G21.A, R_G21.1
unnamed: LED_G22.A, R_G22.1
RED: Q3.1 (G); also elsewhere on the board
YELLOW: Q4.1 (G); also elsewhere on the board

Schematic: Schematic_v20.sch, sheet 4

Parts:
POT1: 3310C-001-503L
Q7: NMOSFET; SOT23
SG1: F/CM12P
SW1: SWITCH_1X1; HDRRAR5W64P200_1X5_1016X736X556B

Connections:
+5V: POT1.3, SG1.+ (1), SW1.2; also elsewhere on the board
BRIGHTNESS: POT1.2; also elsewhere on the board
BUZZER: Q7.1 (G); also elsewhere on the board
BUZZ_EN: SW1.3; also elsewhere on the board
GND: POT1.1, Q7.2 (S), SW1.4; also elsewhere on the board
unnamed: Q7.3 (D), SG1.- (2)

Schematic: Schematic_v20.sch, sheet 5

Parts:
D1: 1N4448W; SOD3715X135
J1: 61400416121
R6: R-EU_R1206; R1206

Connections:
GND: J1.4 (GND); also elsewhere on the board
unnamed 17: D1.1 (C), R6.1; also elsewhere on the board

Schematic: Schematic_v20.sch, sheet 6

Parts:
C6: 100nF; C0603
C7, C8: 22pF; C0603
IC1: ATMEGA328P; TQFP32-08
Q6: 16MHz; HC49UP
SV1: ML6

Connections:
+5V: C6.2, IC1.4 (VCC), IC1.6 (VCC1), IC1.18 (AVCC), IC1.20 (AREF), SV1.2; also elsewhere on the board
/RES: IC1.29 (PC6(!RESET!/PCINT14)), SV1.5; also elsewhere on the board
BRIGHTNESS: IC1.24 (PC1(ADC1/PCINT9)); also elsewhere on the board
BUZZER: IC1.14 (PB2(PCINT2/!SS!/OC1B)); also elsewhere on the board
BUZZ_EN: IC1.2 (PD4(PCINT20/XCK/T0)); also elsewhere on the board
GND: C6.1, C7.1, C8.1, IC1.3 (GND), IC1.5 (GND1), IC1.21 (GND2), SV1.6; also elsewhere on the board
GREEN: IC1.10 (PD6(PCINT22/OC0A/AIN0)); also elsewhere on the board
MISO: IC1.16 (PB4(PCINT4/MISO)), SV1.1
MOSI: IC1.15 (PB3(PCINT3/OC2A/MOSI)), SV1.4
unnamed: C7.2, IC1.7 (PB6(PCINT6/XTAL1/TOSC1)), Q6.2
unnamed: C8.2, IC1.8 (PB7(PCINT7/XTAL2/TOSC2)), Q6.1
PWM: IC1.23 (PC0(ADC0/PCINT8)); also elsewhere on the board
RDY: IC1.32 (PD2(INT0/PCINT18)); also elsewhere on the board
RED: IC1.1 (PD3(PCINT19/OC2B/INT1)); also elsewhere on the board
SCK: IC1.17 (PB5(SCK/PCINT5)), SV1.3
SCL: IC1.28 (PC5(ADC5/SCL/PCINT13)); also elsewhere on the board
SDA: IC1.27 (PC4(ADC4/SDA/PCINT12)); also elsewhere on the board
VALUE: IC1.25 (PC2(ADC2/PCINT10))
YELLOW: IC1.9 (PD5(PCINT21/OC0B/T1)); also elsewhere on the board

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
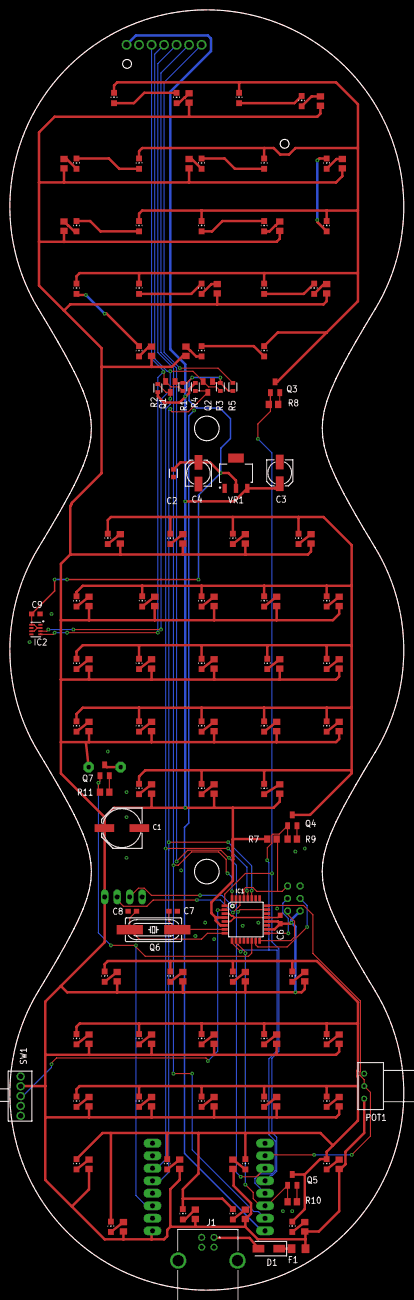
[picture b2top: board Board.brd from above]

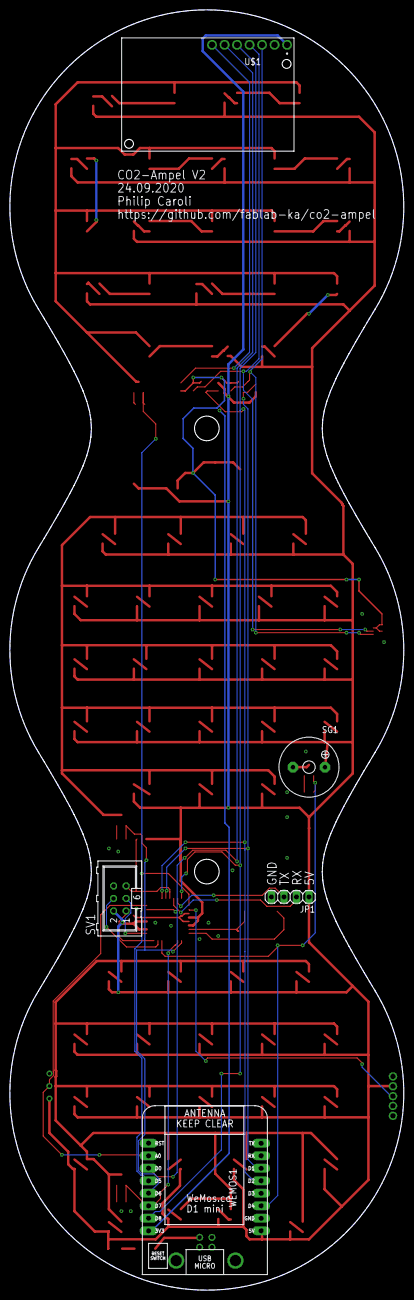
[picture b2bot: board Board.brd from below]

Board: 2 copper layers, 80.0 x 260.0 mm, 159 parts (5 on the bottom side), 96 nets.

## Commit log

2020-08-29 added bom+gerber
2020-09-01 corrected typo
2020-09-24 Prototyp 2
2020-10-14 add smiley.svg
2020-10-15 Updated version
    Prototyp 2
2020-10-25 Initial release
2020-10-25 smiley for Silhouette Studio
2020-10-25 80 smileys: SVG + Silhouette Studio
2020-10-25 added openscad case
2020-10-25 moved plotter files in subdir
2020-10-25 added images
2020-10-25 added image v2
2020-10-27 Add documentation overview
2020-10-27 added BOM PCBv2
2020-10-27 renanmed BOM
2020-10-27 added tools, bom link
2020-10-27 fixed link
2020-10-27 fixed typo
2020-10-27 added links, moved BOM
2020-10-27 fixed links
2020-10-27 was designed for pcb v1
2020-10-27 removed v1 files
2020-10-28 fixed dupes
2020-10-28 Added initial instruction manual
2020-10-28 changed lower hysterese threshhold
2020-10-29 Improve instruction manual
2020-10-29 Correct formatting issues
2020-10-29 Correct more formatting issues
2020-10-29 BOM/CPL für jlcpcb
    Bestückungsliste und Pick+Place-Liste für jlcpcb.com hinzugefügt
2020-11-01 changed default mqtt hostname
2020-11-01 improved outline
2020-11-02 get organisation from retained mqtt topic instead from config file
2020-11-02 added screencast
2020-11-02 added diffusor
2020-11-04 added second show, due to problems with leds turned on during setup phase
2020-11-04 added requirements
2020-11-04 added version for each library
2020-11-05 fixed syntax
2020-11-08 new features: backup.json, send config.json via mqtt, start calibration via mqtt, reset co2 sensor (untested)
2020-11-08 increased co2 timout
2020-11-08 fixed wrong constant name
2020-11-08 default PCBV2
2020-11-08 added resetwifi, option to disable selftest, 1x white blink: wifi connected
2020-11-08 added fusion v3 case
2020-11-08 fixed json syntax
2020-11-09 changed red threshold due to recommended values in KA and Bavaria
2020-11-09 added calibration feature via switch
2020-11-10 added ota update; brightnes via config.json
2020-11-10 Add platformio
2020-11-10 updated ArduinoJson version
2020-11-11 Update ArduinoJson version in platformio as well
2020-11-11 commented out EE895
2020-11-12 Update Bedienungsanleitung.md
    changed thresholds
2020-11-13 Added kit documentation
2020-11-13 Update README.md
    removed wrong switch
2020-11-14 Update README.md
    added correct switch
2020-11-15 replaced adafruit neopixel lib with fastled lib
2020-11-15 changed default brightnes, due to new range (0-255 instead of 0-100)
2020-11-16 added tool for scd30 soldering
2020-11-16 fixed for pcbv1
2020-11-17 replace yellow
2020-11-27 fixed led colors
2020-11-27 don't print error message if bmp280 ist disabled in config file
2020-11-28 improved calibration
2020-12-01 changed calibration ppm due to https://www.icos-cp.eu/data-products/ATM_NRT_CO2_CH4
2020-12-02 added compile/upload instructions
2020-12-10 Update README.md
    fixed two typos
2020-12-10 set calibration ppm via config file
2020-12-10 switch disabled only the buzzer if wifi is not connected
2020-12-10 changed data privacy infos
2020-12-10 added missing tag in config file
2020-12-20 added support for bme280
2020-12-20 added adafruit bm280 lib
2020-12-20 updated config.json for v7
2020-12-25 Updated all files for PCBv4.1
2020-12-25 fixed format
2020-12-25 added bmp280 link
2021-03-19 added soldering documentation
2021-03-19 added more images
2021-03-19 fixed typos
2021-03-22 splitted in 7 parts
2021-03-23 fixed image alignment
2021-03-23 moved cutting to part I and added warning
2021-03-23 added missing images for part IV
2021-03-23 added missing reference
2021-03-23 added links to soldering documentation
2021-03-23 added link
2021-03-23 added short circuit tests

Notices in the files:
parts and their libraries:
Wurth_Connectors_WR-USB: Copyright: Würth Elektronik
COPYRIGHT: Copyright (C) 2016 Accelerated Designs. All rights reserved
